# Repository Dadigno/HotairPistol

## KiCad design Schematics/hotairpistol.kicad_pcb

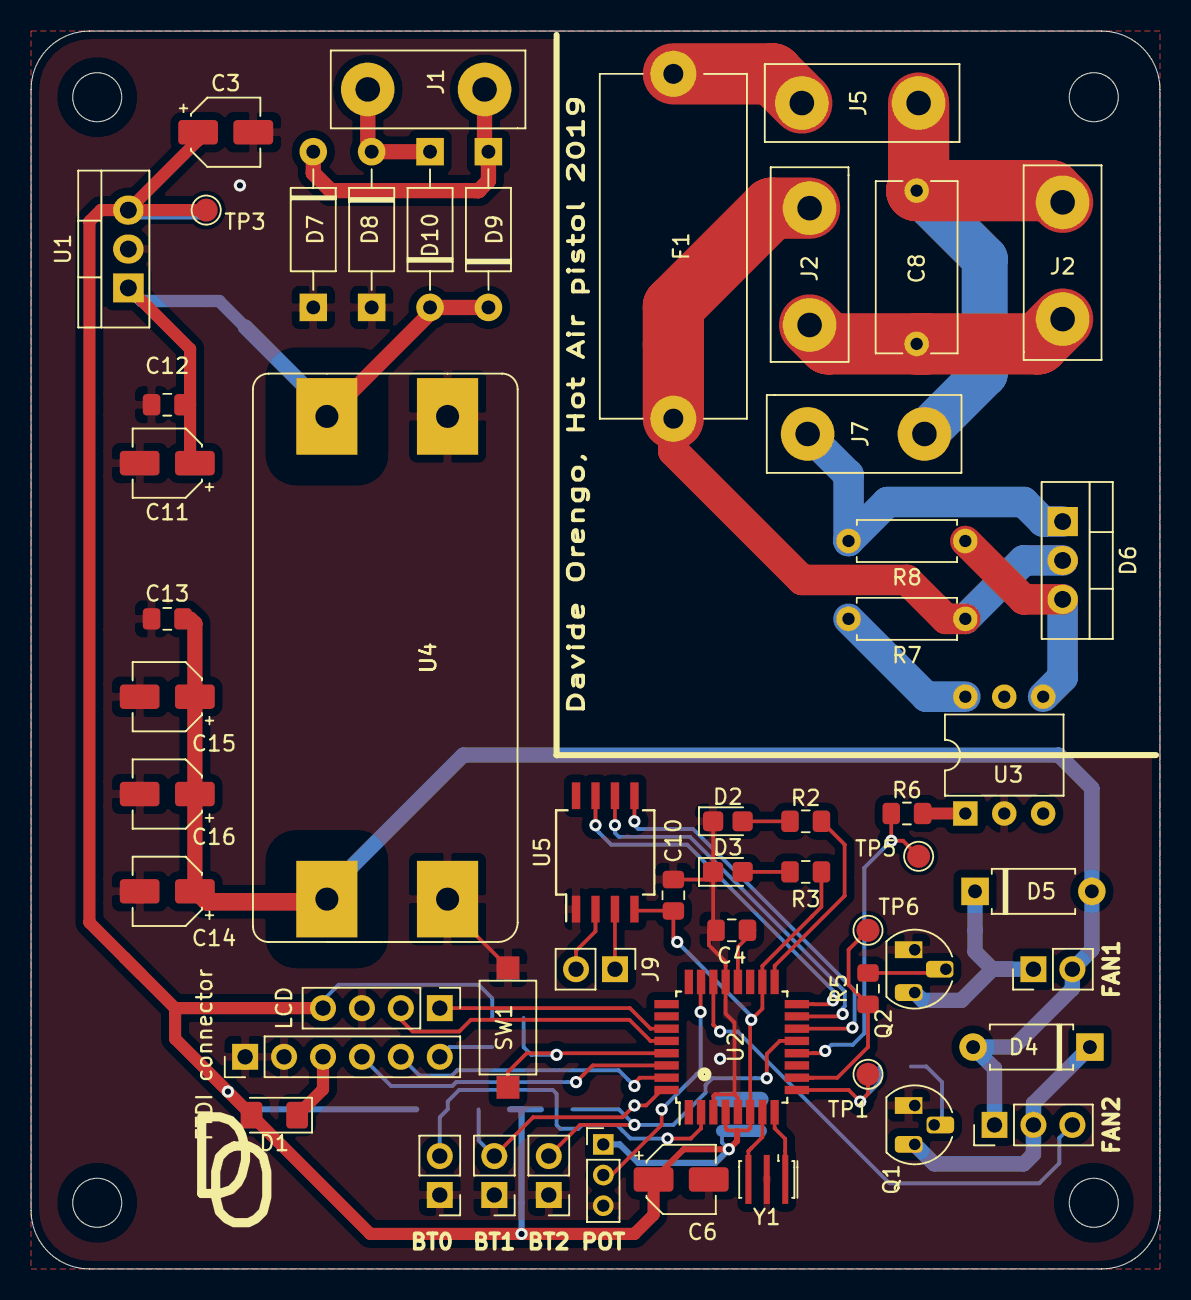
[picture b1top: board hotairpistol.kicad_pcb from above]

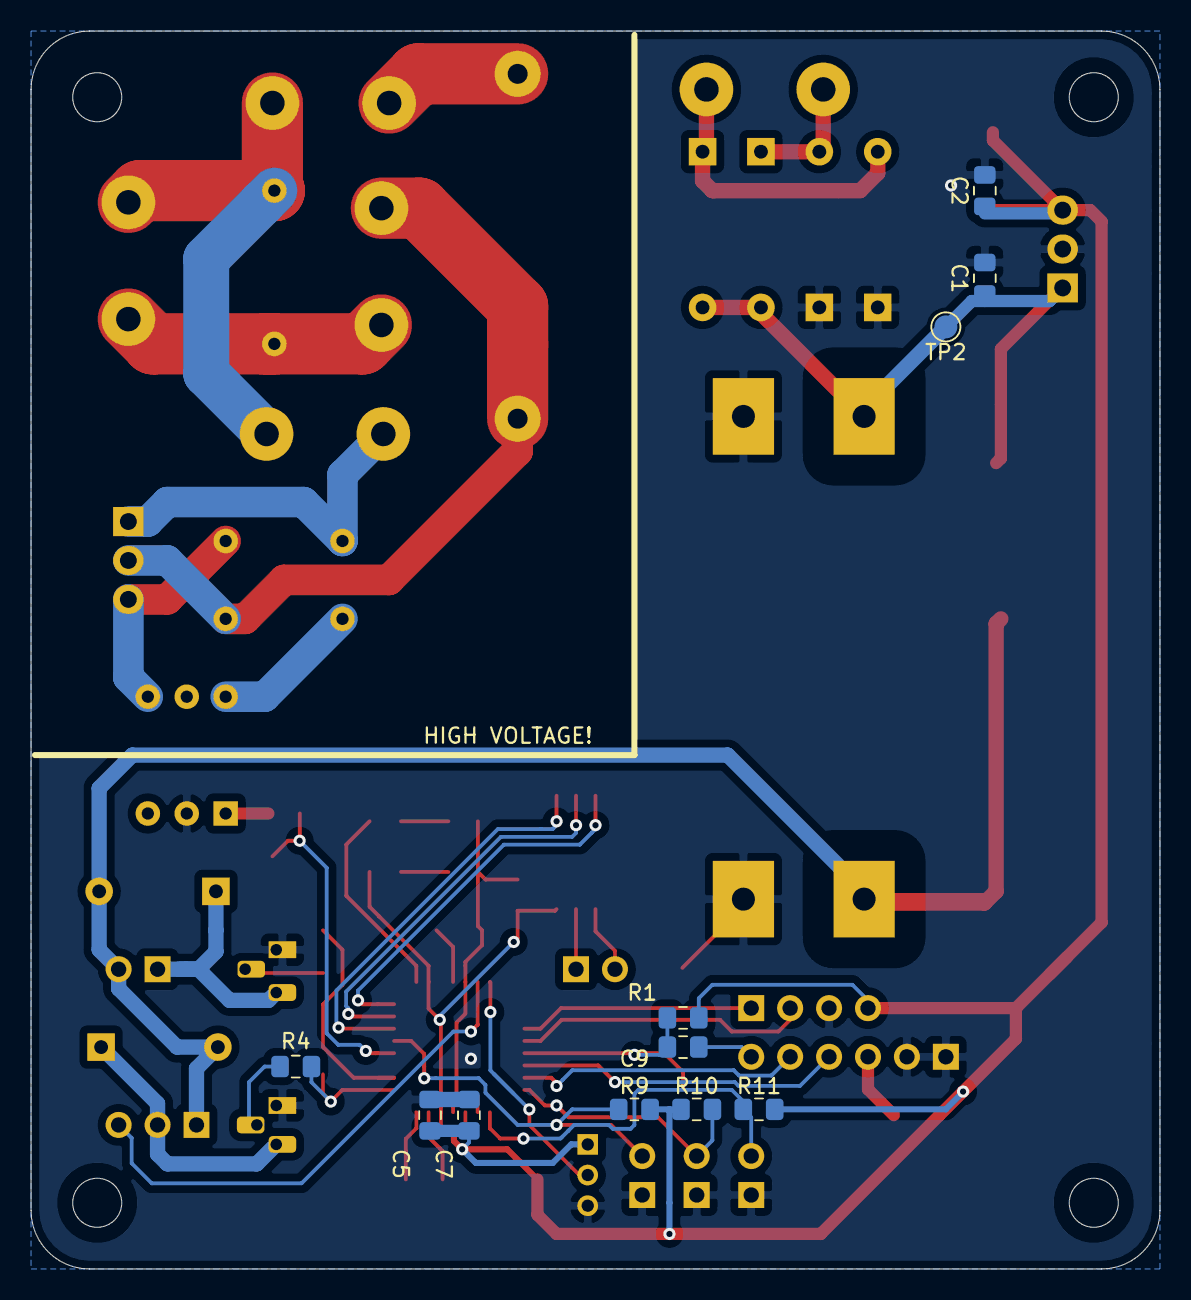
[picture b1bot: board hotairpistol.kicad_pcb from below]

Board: 2 copper layers, 73.7 x 80.8 mm, 70 parts (11 on the bottom side), 43 nets.

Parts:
C1, C2, C4, C5, C7, C9, C12, C13: 100n; C_0805_2012Metric_Pad1.15x1.40mm_HandSolder
C3, C6, C11, C14, C15, C16: 10u; CP_Elec_4x5.4
C8: MKP 100n; C_Rect_L11.0mm_W5.1mm_P10.00mm_MKT
C10: 0.1u; C_0805_2012Metric_Pad1.15x1.40mm_HandSolder
D1: DIODE; D_1206_3216Metric_Pad1.42x1.75mm_HandSolder
D2, D3: LED; LED_0805_2012Metric_Castellated
D4, D5: DIODE; D_A-405_P7.62mm_Horizontal
D6: BTA140-800; TO-220-3_Vertical
D7, D8, D9, D10: DIODE; D_A-405_P10.16mm_Horizontal
F1: Fuse; Fuseholder_Cylinder-5x20mm_Schurter_0031_8201_Horizontal_Op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
H1, H2, H3, H4: MountingHole; MountingHole_3.2mm_M3
J1: Trafo out; holes_220v
J2: Line; holes_220v
J3: Fan cooler; PinHeader_1x03_P2.54mm_Vertical
J4: Fan heater; PinHeader_1x02_P2.54mm_Vertical
J5: Trafo in; holes_220v
J6: LCD; PinHeader_1x04_P2.54mm_Vertical
J7: Heater; holes_220v
J8: FTDI connector; PinHeader_1x06_P2.54mm_Vertical
J9: Thermocouple; PinHeader_1x02_P2.54mm_Vertical
Q1, Q2: 2n2222; TO-92_HandSolder
R1, R9, R10, R11: 10k; R_0805_2012Metric_Pad1.15x1.40mm_HandSolder
R2, R3, R6: 1k; R_0805_2012Metric_Pad1.15x1.40mm_HandSolder
R4: 2,2k; R_0805_2012Metric_Pad1.15x1.40mm_HandSolder
R5: 2.2k; R_0805_2012Metric_Pad1.15x1.40mm_HandSolder
R7: 360; R_Axial_DIN0207_L6.3mm_D2.5mm_P7.62mm_Horizontal
R8: 330; R_Axial_DIN0207_L6.3mm_D2.5mm_P7.62mm_Horizontal
RV1: R_POT; PinHeader_1x03_P2.00mm_Vertical
SW1: SW_Push; SW_SPST_CK_RS282G05A3
SW2: SW_Push; holes_220v
SW3: BT1; PinHeader_1x02_P2.54mm_Vertical
SW4: BT2; PinHeader_1x02_P2.54mm_Vertical
SW5: SW_Reed; PinHeader_1x02_P2.54mm_Vertical
TP1: TF1; TestPoint_Pad_D1.5mm
TP2, TP3, TP5: TestPoint; TestPoint_Pad_D1.5mm
TP6: TF2; TestPoint_Pad_D1.5mm
U1: L7805; TO-220-3_Vertical
U2: ATmega328-AU; TQFP-32_7x7mm_P0.8mm
U3: MOC3063M; DIP-6_W7.62mm
U4: MT3608; MT3608_DCDC_BUCK_BOOST
U5: MAX6675; SO-8_5.3x6.2mm_P1.27mm
Y1: Crystal_GND2; Resonator_SMD_muRata_CSTxExxV-3Pin_3.0x1.1mm_HandSoldering

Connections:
+5V: C2.1, C3.1, C5.1, C6.1, C7.1, C10.1, D1.2, J6.4, R1.1, R3.2, R9.1, R10.1, R11.1, RV1.1, TP3.1, U1.3, U2.4, U2.6, U2.18, U5.4
+24V: C13.2, C14.1, C15.1, C16.1, D4.2, D5.2, J3.1, J4.2, U4.3
/220-L: D6.2, F1.2, R7.1, SW2.2
/220-N: C8.1, J2.1, J5.2, J7.1
/A0: RV1.2, U2.23
/A4\SDA: J6.1, U2.27
/A5\SCL: J6.2, U2.28
/D0\RX: J8.4, U2.30
/D1\TX: J8.5, U2.31
/D2: R10.2, SW3.2, U2.32
/D4: R11.2, SW5.2, U2.2
/D5: R4.2, TP1.1, U2.9
/D6: R5.2, TP6.1, U2.10
/D8: R6.2, TP5.1, U2.12
/D9: R9.2, SW4.2, U2.13
/D10: U2.14, U5.5
/D11\MOSI: U2.15, U5.6
/D12\MISO: U2.16, U5.7
/D13\SCK: R2.1, U2.17
/FAN1-: D4.1, J3.2, Q1.2
/FAN2-: D5.1, J4.1, Q2.2
/RESET: C9.1, R1.2, SW1.1, U2.29
/V+: D7.2, D9.1, J1.2
/V-: D8.2, D10.1, J1.1
Earth: C1.2, C2.2, C3.2, C4.2, C5.2, C6.2, C7.2, C10.2, C11.2, C12.2, C13.1, C14.2, C15.2, C16.2, D2.1, D3.1, D7.1, D8.1, J6.3, J8.1, J8.2, Q1.3, Q2.3, RV1.3, SW1.2, SW3.1, SW4.1, SW5.1, U1.2, U2.3, U2.5, U2.21, U3.2, U4.2, U4.4, U5.1, Y1.2
unnamed: C1.1, C11.1, C12.1, D9.2, D10.2, TP2.1, U1.1, U4.1
unnamed: C4.1, U2.20
unnamed: C8.2, J2.2, SW2.1
unnamed: C9.2, J8.6
unnamed: D2.2, R2.2
unnamed: D3.2, R3.1
unnamed: D6.1, J7.2, R8.2
unnamed: D6.3, R8.1, U3.4
unnamed: F1.1, J5.1
unnamed: J9.1, U5.3
unnamed: J9.2, U5.2
unnamed: Q1.1, R4.1
unnamed: Q2.1, R5.1
unnamed: R6.1, U3.1
unnamed: R7.2, U3.6
unnamed: U2.7, Y1.3
unnamed: U2.8, Y1.1
VBUS: D1.1, J8.3

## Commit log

2020-02-04 code file uploaded
    it works!
2020-05-31 deleted old files
2020-05-31 project revisioned added
2020-05-31 hot air pistol
2020-05-31 Removed linkage to local libraries
2021-05-24 Update hotairpistol.ino
    To comply with the patched pcb
